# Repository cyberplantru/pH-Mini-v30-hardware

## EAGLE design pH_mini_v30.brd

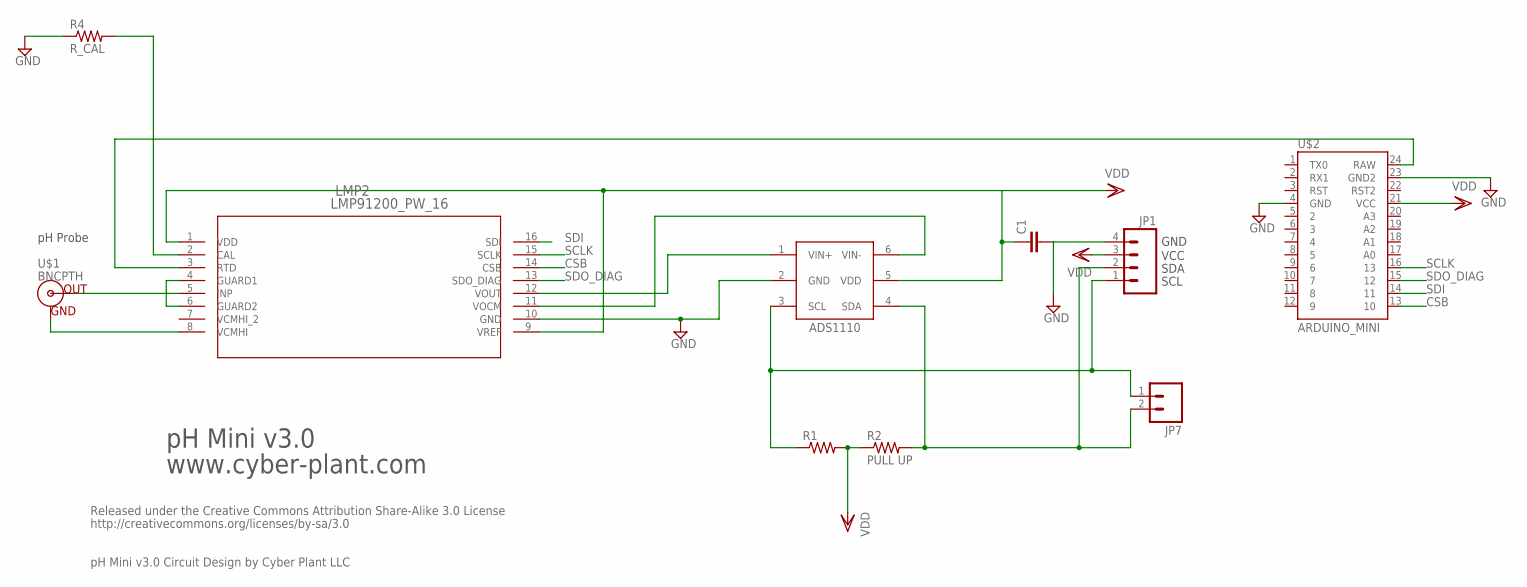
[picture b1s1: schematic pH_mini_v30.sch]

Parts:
C1: CAP1206; 1206
IC1: ADS1110; SOT-23-6
JP1: M04PTH; 1X04
JP7: M02PTH; 1X02
LMP2: LMP91200_PW_16; MTC16
R1: R-US_0207/10; 0207/10
R2: PULL UP; 0207/10
R4: R_CAL; 0207/10
U$1: BNCPTH; BNC
U$2: ARDUINO_MINI

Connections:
CSB: LMP2.14 (CSB), U$2.13 (10)
GND: C1.2, IC1.2 (GND), JP1.4, LMP2.10 (GND), R4.1, U$2.4 (GND), U$2.23 (GND2)
unnamed: IC1.1 (VIN+), LMP2.12 (VOUT)
unnamed: IC1.6 (VIN-), LMP2.11 (VOCM)
unnamed: LMP2.3 (RTD), U$2.24 (RAW)
unnamed: LMP2.8 (VCMHI), U$1.GND
unnamed: LMP2.5 (INP), U$1.S (OUT)
unnamed: LMP2.2 (CAL), R4.2
unnamed: LMP2.4 (GUARD1), LMP2.6 (GUARD2)
SCL: IC1.3 (SCL), JP1.1, JP7.1, R1.1
SCLK: LMP2.15 (SCLK), U$2.16 (13)
SDA: IC1.4 (SDA), JP1.2, JP7.2, R2.2
SDI: LMP2.16 (SDI), U$2.14 (11)
SDO_DIAG: LMP2.13 (SDO_DIAG), U$2.15 (12)
VDD: C1.1, IC1.5 (VDD), JP1.3, LMP2.1 (VDD), LMP2.9 (VREF), R1.2, R2.1, U$2.21 (VCC)

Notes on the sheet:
pH Probe
GND
VCC
SDA
SCL
pH Mini v3.0
www.cyber-plant.com
Released under the Creative Commons Attribution Share-Alike 3.0 License
http://creativecommons.org/licenses/by-sa/3.0
pH Mini v3.0 Circuit Design by Cyber Plant LLC

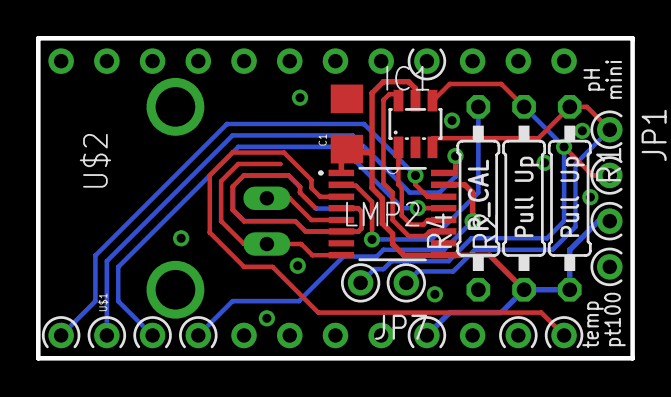
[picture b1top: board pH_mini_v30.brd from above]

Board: 2 copper layers, 33.0 x 17.8 mm, 10 parts (0 on the bottom side), 15 nets.

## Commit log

2016-06-09 :space_invader: Added .gitattributes & .gitignore files
2016-06-09 master

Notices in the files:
parts and their libraries:
Arduinominimi: Licensing: CC v3.0 Share-Alike You are welcome to use this library for commercial purposes.
